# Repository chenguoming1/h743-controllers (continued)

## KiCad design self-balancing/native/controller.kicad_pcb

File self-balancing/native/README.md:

# Current native repair (2026-10-04)

This working native board is the DRC/physical-copper repair of main `491987e`. See [the current repair review](review/usb-routing-491987e/README.md) for exact source hash, checks, measured USB-C orientation skew, and bounded fanout rules.

**Native CAD checks pass, but this is not a regenerated manufacturing release.** Existing P6 Gerbers, supplier reports, manifests and source-hash export guard remain historical and unchanged. Do not fabricate from stale exports or bypass that guard. Component placement, CPL, BOM, schematics and local libraries are preserved.

---

## Historical P6 package description (not qualification of the current native hash)

# R3-S6-P6 controller

**Use this P6 package only. It supersedes all earlier fabrication packages. P5 contained confirmed narrow copper attachments and must not be fabricated.**

This is the final prototype PCB submission package for the 38 × 38 mm, six-layer H743 controller. Its current electrical map, component placement, 67 edge pads, side sockets, corrected supplier CPL and USB pair geometry are retained. Fabricate with the exact settings in `documents/P6-Production-Instructions.txt`; the assembly production approvals listed there must precede assembly.

The whole-board review covers all 85 routed nets and every copper layer. It simplifies coherent paths, removes unnecessary hooks and dead trees, repairs actual copper necks at joins/pads/vias, and retires six redundant signal vias. It retains justified obstacle escapes and the ground returns. The final source has 3,178 track segments and 406 vias, including all 97 ground stitches. It is 61.696 mm shorter than P5. Those counts supplement the actual geometry and visual evidence; they are not the acceptance test by themselves.

## What to use

The paths below are relative to the release ZIP root.

- `native/`: KiCad source, project libraries and the mandatory P6 export guard
- `release/single-board-gerbers/`: the current six-layer Gerbers, plated and nonplated drills, and job file
- `release/assembly/JLC_BOM.csv` and `JLC_CPL.csv`: 35 part groups and 79 placements; the CPL preserves the user's corrections
- `documents/`: schematic, assembly drawing, fabrication review and production instructions
- `native/review/routing-visual-review/index.html`: complete offline net-by-net visual atlas; unzip first, then open this file
- `validation/`: independent native, actual-copper, exported-file and supplier evidence
- `reconstruction/`: reproducible delta and historical input, for audit only; never fabricate that input

The ZIP manifest fixes every included byte. Final source SHA-256: `cf16a6f5ceae65aad217e29eef23a60dbc8f15af743b363df03aa5a42c9c71dc`. The final supplier project is https://jlcdfm.com/viewer?pcbUploadFileId=629361373570224129. Trace width and spacing are green; all three former hole-to-trace advisories cleared. The report gives the evidence-backed dispositions for remaining process/model alerts, including the unchanged 24 red / 6 yellow SMT records. These counts do not constitute assembly production approval.

## Readiness limits

Bare-PCB submission uses a specified supported process. Assembly still requires the supplier's final two-face placement/polarity drawing, a suitable carrier/support arrangement, an approved production stencil, and soldering all four USB shell anchors. The supplier regenerates its stencil, so the real U2/U11 split apertures must be requested explicitly. The package includes the concrete instructions; it does not claim an order or supplier production approval already exists.

First-article inspection and current-limited electrical, thermal, USB/firmware, connector and application tests remain necessary. Compilation and CAD checks do not establish flight readiness or a numerical probability of success.

## Regeneration

Use `native/tools/export_release_p6.py` only with its exact source/evidence guard. It refuses stale source and requires actual join, pad, via, plane and dangling-tree checks. `export_release.py` is the underlying producer, not an alternative release-acceptance path. Preserved older helpers and baselines are historical provenance.

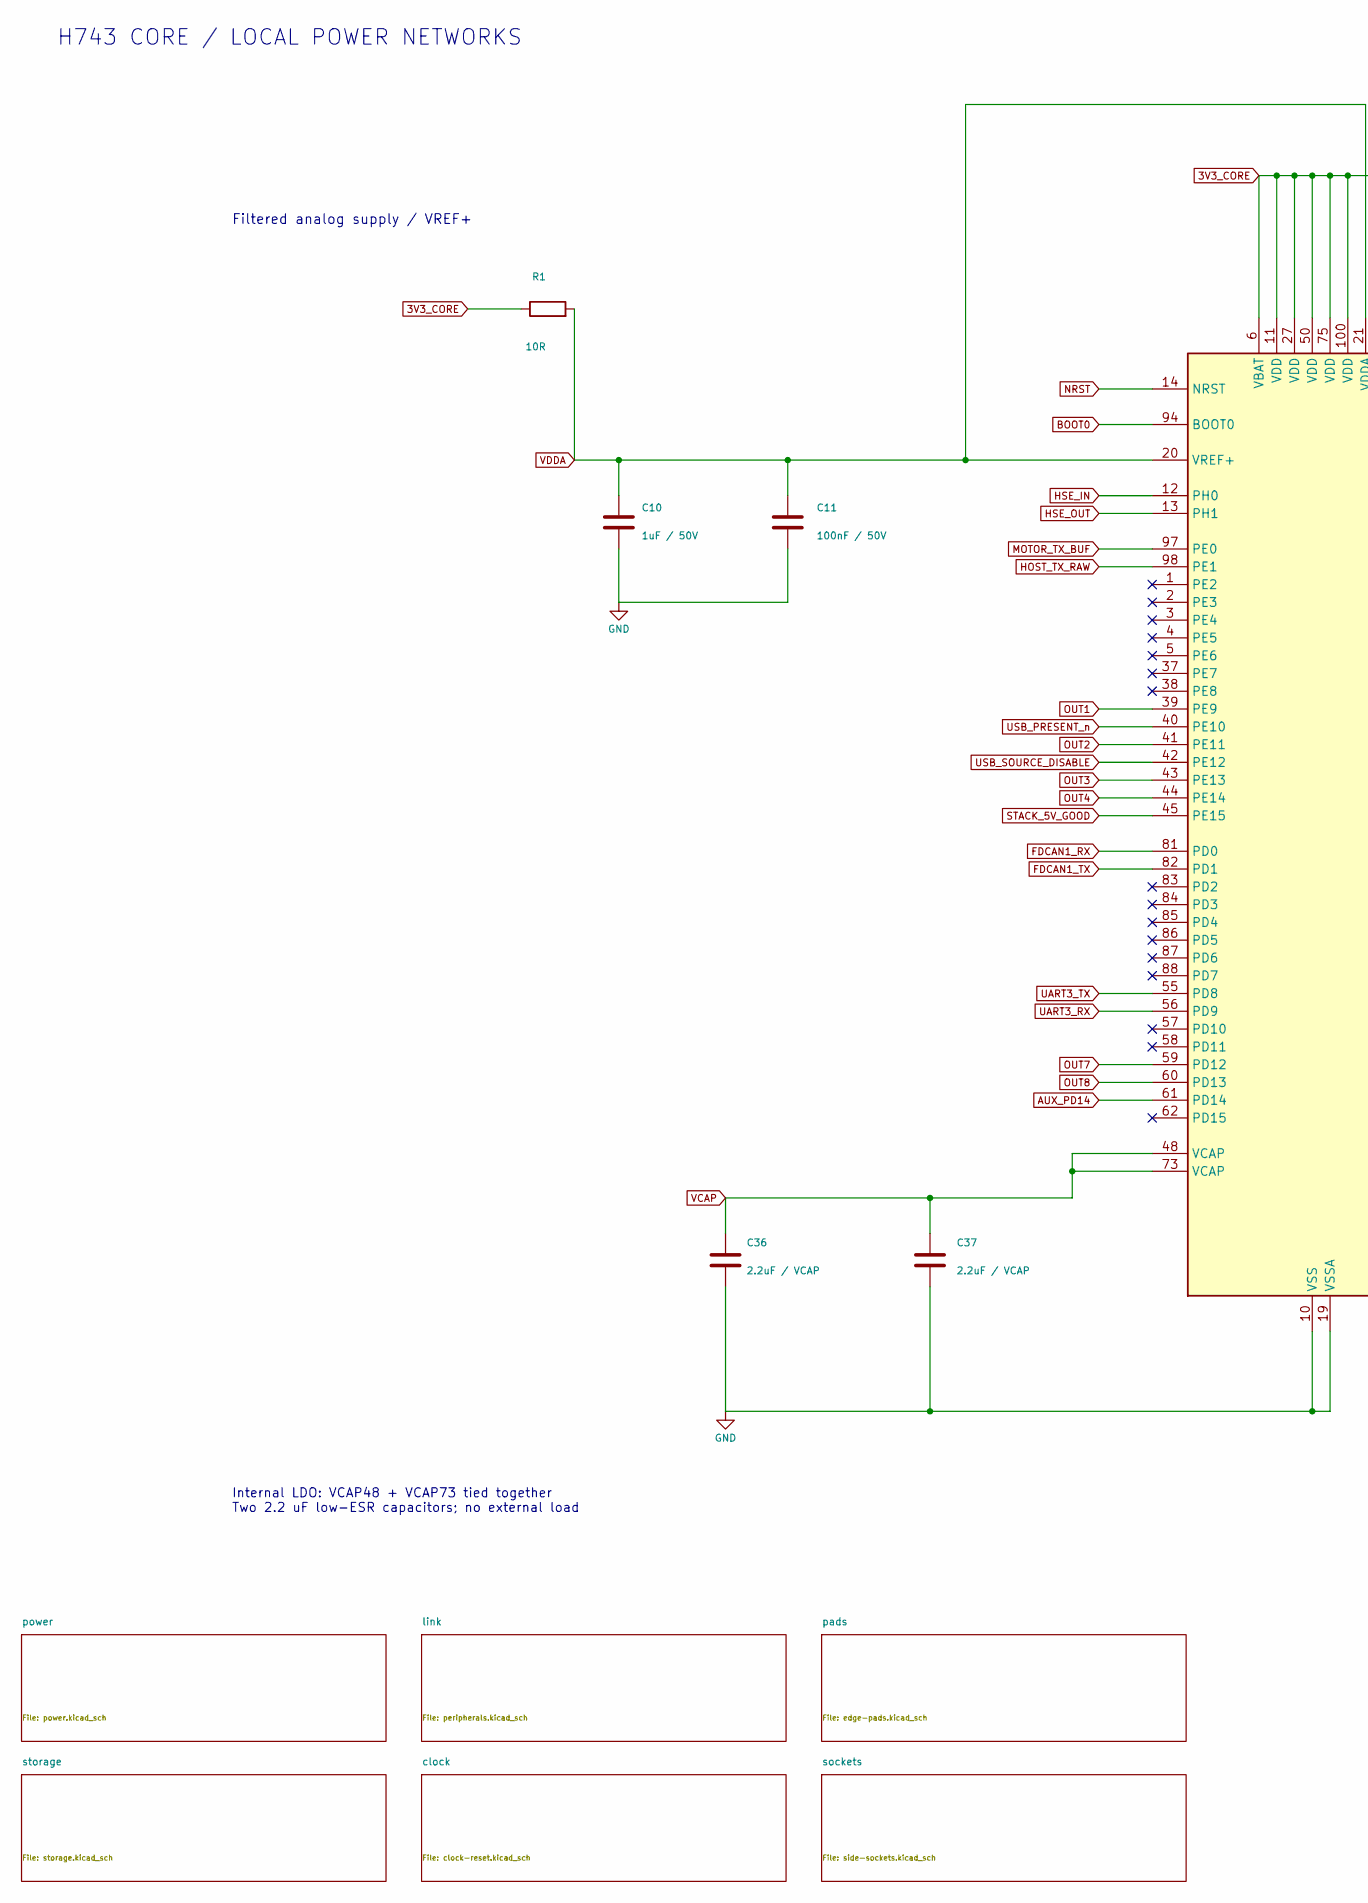
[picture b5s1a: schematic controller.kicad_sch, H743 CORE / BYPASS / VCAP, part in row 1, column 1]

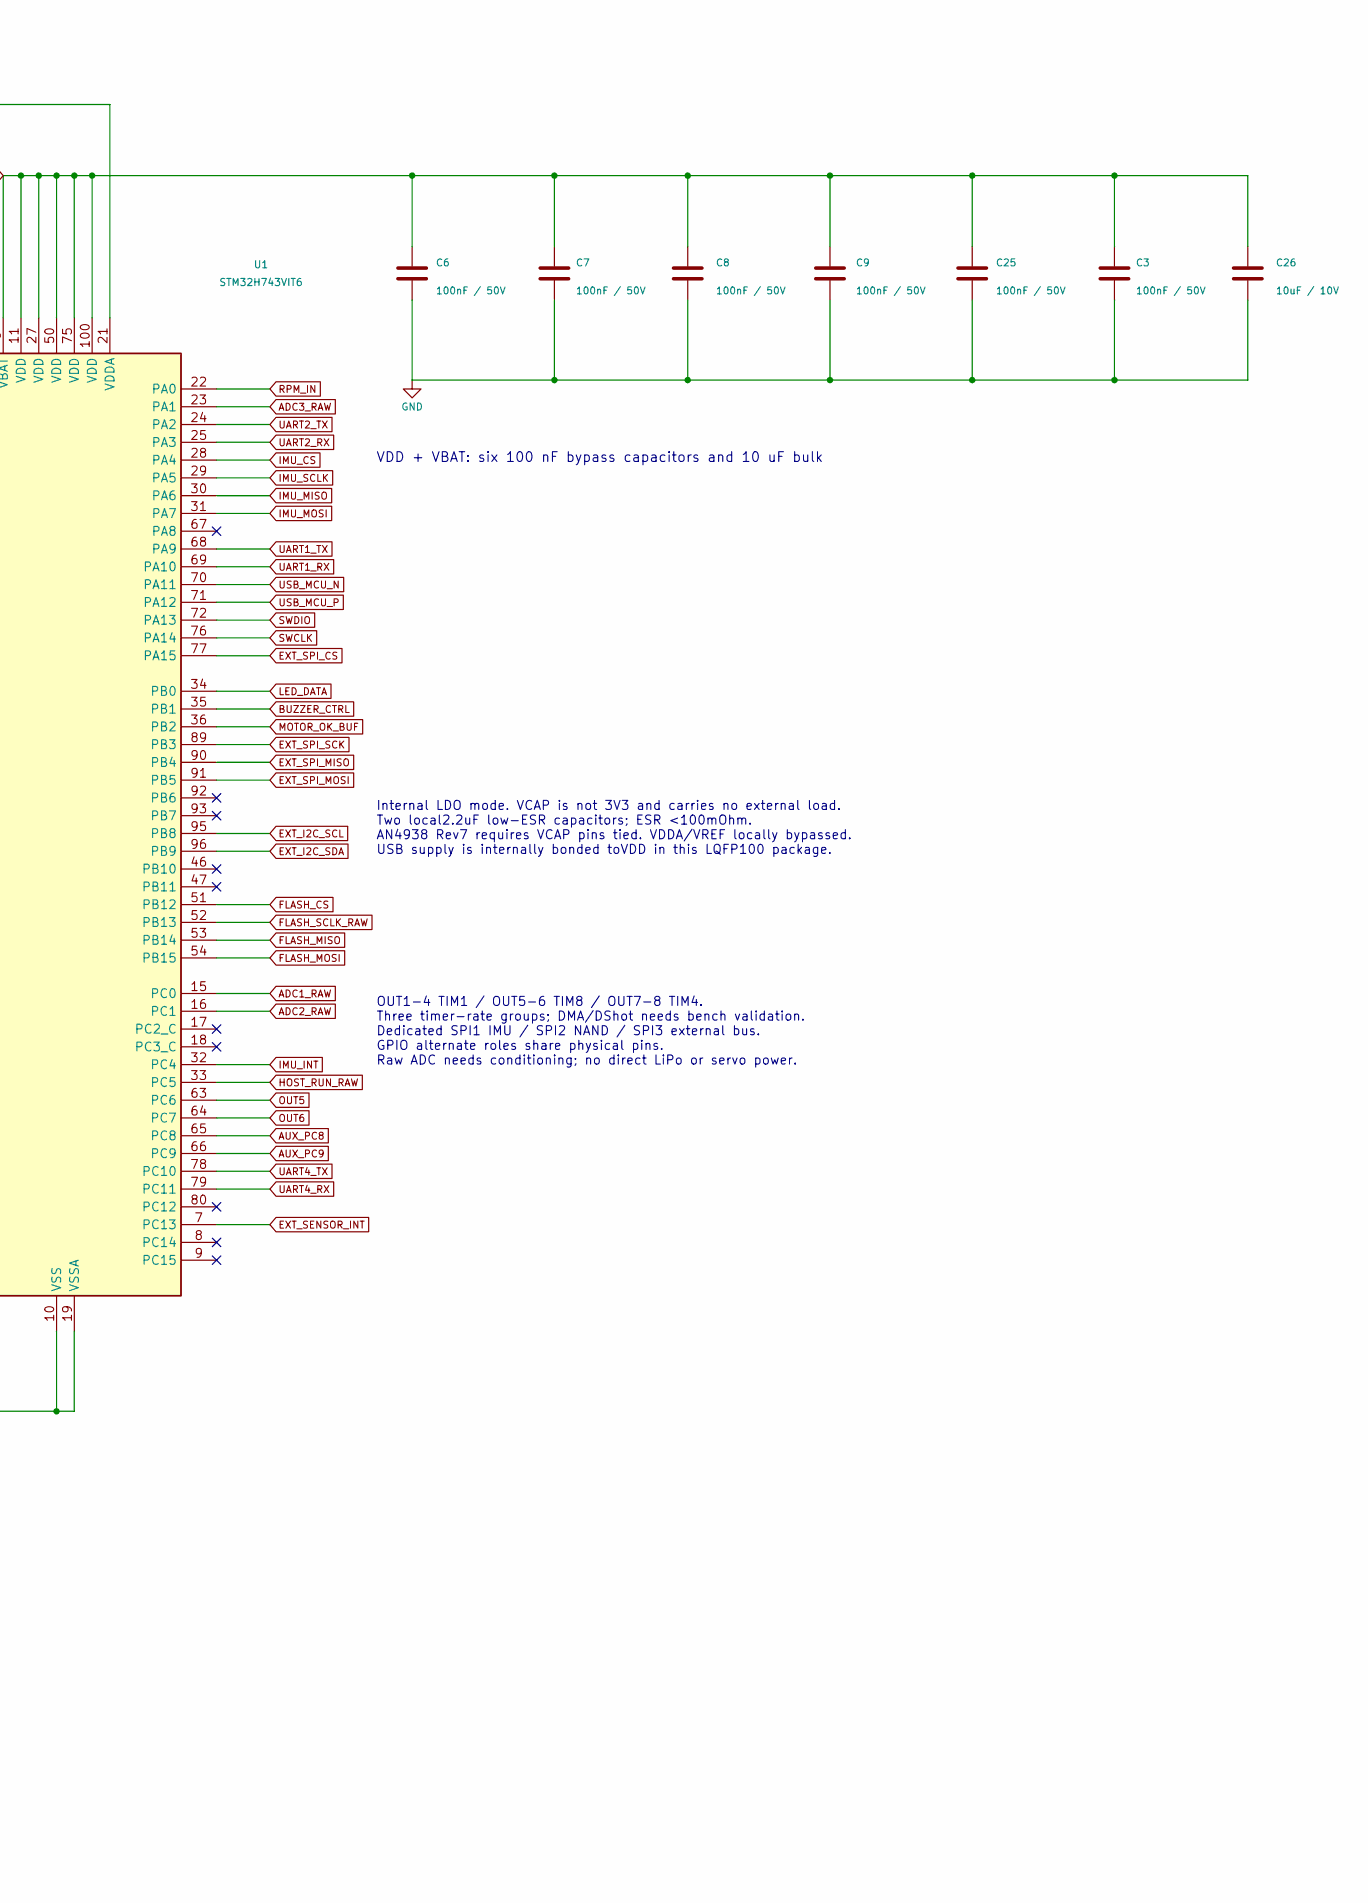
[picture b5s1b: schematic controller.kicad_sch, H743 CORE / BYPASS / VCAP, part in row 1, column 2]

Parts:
C3: 100nF / 50V; C3_C_0603_1608Metric; Manufacturer_Part_Number CC0603KRX7R9BB104; LCSC C14663
C6: 100nF / 50V; C6_C_0603_1608Metric; Manufacturer_Part_Number CC0603KRX7R9BB104; LCSC C14663
C7: 100nF / 50V; C7_C_0603_1608Metric; Manufacturer_Part_Number CC0603KRX7R9BB104; LCSC C14663
C8: 100nF / 50V; C8_C_0603_1608Metric; Manufacturer_Part_Number CC0603KRX7R9BB104; LCSC C14663
C9: 100nF / 50V; C9_C_0603_1608Metric; Manufacturer_Part_Number CC0603KRX7R9BB104; LCSC C14663
C10: 1uF / 50V; C10_C_0603_1608Metric; Manufacturer_Part_Number CL10A105KB8NNNC; LCSC C15849
C11: 100nF / 50V; C11_C_0603_1608Metric; Manufacturer_Part_Number CC0603KRX7R9BB104; LCSC C14663
C25: 100nF / 50V; C25_C_0603_1608Metric; Manufacturer_Part_Number CC0603KRX7R9BB104; LCSC C14663
C26: 10uF / 10V; C26_C_0603_1608Metric; Manufacturer_Part_Number CL10A106KP8NNNC; LCSC C19702
C36: 2.2uF / VCAP; C36_C_0603_1608Metric; Manufacturer_Part_Number CL10A225KO8NNNC; LCSC C23630
C37: 2.2uF / VCAP; C37_C_0603_1608Metric; Manufacturer_Part_Number CL10A225KO8NNNC; LCSC C23630
R1: 10R; R1_R_0603_1608Metric; Manufacturer_Part_Number 0603WAF100JT5E; LCSC C22859
U1: STM32H743VIT6; U1_LQFP-100_14x14mm_P0.5mm; Manufacturer_Part_Number STM32H743VIT6; LCSC C114409

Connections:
ADC1_RAW: U1.15 (PC0); also elsewhere on the board
ADC2_RAW: U1.16 (PC1); also elsewhere on the board
ADC3_RAW: U1.23 (PA1); also elsewhere on the board
AUX_PC8: U1.65 (PC8); also elsewhere on the board
AUX_PC9: U1.66 (PC9); also elsewhere on the board
AUX_PD14: U1.61 (PD14); also elsewhere on the board
BOOT0: U1.94 (BOOT0); also elsewhere on the board
BUZZER_CTRL: U1.35 (PB1); also elsewhere on the board
EXT_I2C_SCL: U1.95 (PB8); also elsewhere on the board
EXT_I2C_SDA: U1.96 (PB9); also elsewhere on the board
EXT_SENSOR_INT: U1.7 (PC13); also elsewhere on the board
EXT_SPI_CS: U1.77 (PA15); also elsewhere on the board
EXT_SPI_MISO: U1.90 (PB4); also elsewhere on the board
EXT_SPI_MOSI: U1.91 (PB5); also elsewhere on the board
EXT_SPI_SCK: U1.89 (PB3); also elsewhere on the board
FDCAN1_RX: U1.81 (PD0); also elsewhere on the board
FDCAN1_TX: U1.82 (PD1); also elsewhere on the board
FLASH_MISO: U1.53 (PB14); also elsewhere on the board
FLASH_MOSI: U1.54 (PB15); also elsewhere on the board
FLASH_SCLK_RAW: U1.52 (PB13); also elsewhere on the board
GND: C3.2, C6.2, C7.2, C8.2, C9.2, C10.2, C11.2, C25.2, C26.2, C36.2, C37.2, U1.10 (VSS), U1.19 (VSSA), U1.26 (VSS), U1.49 (VSS), U1.74 (VSS), U1.99 (VSS); also elsewhere on the board
HOST_RUN_RAW: U1.33 (PC5); also elsewhere on the board
HOST_TX_RAW: U1.98 (PE1); also elsewhere on the board
HSE_IN: U1.12 (PH0); also elsewhere on the board
HSE_OUT: U1.13 (PH1); also elsewhere on the board
IMU_CS: U1.28 (PA4); also elsewhere on the board
IMU_INT: U1.32 (PC4); also elsewhere on the board
IMU_MISO: U1.30 (PA6); also elsewhere on the board
IMU_MOSI: U1.31 (PA7); also elsewhere on the board
IMU_SCLK: U1.29 (PA5); also elsewhere on the board
LED_DATA: U1.34 (PB0); also elsewhere on the board
MOTOR_OK_BUF: U1.36 (PB2); also elsewhere on the board
MOTOR_TX_BUF: U1.97 (PE0); also elsewhere on the board
NRST: U1.14 (NRST); also elsewhere on the board
OUT1: U1.39 (PE9); also elsewhere on the board
OUT2: U1.41 (PE11); also elsewhere on the board
OUT3: U1.43 (PE13); also elsewhere on the board
OUT4: U1.44 (PE14); also elsewhere on the board
OUT5: U1.63 (PC6); also elsewhere on the board
OUT6: U1.64 (PC7); also elsewhere on the board
OUT7: U1.59 (PD12); also elsewhere on the board
OUT8: U1.60 (PD13); also elsewhere on the board
RPM_IN: U1.22 (PA0); also elsewhere on the board
STACK_5V_GOOD: U1.45 (PE15); also elsewhere on the board
SWCLK: U1.76 (PA14); also elsewhere on the board
SWDIO: U1.72 (PA13); also elsewhere on the board
UART1_RX: U1.69 (PA10); also elsewhere on the board
UART1_TX: U1.68 (PA9); also elsewhere on the board
UART2_RX: U1.25 (PA3); also elsewhere on the board
UART2_TX: U1.24 (PA2); also elsewhere on the board
UART3_RX: U1.56 (PD9); also elsewhere on the board
UART3_TX: U1.55 (PD8); also elsewhere on the board
UART4_RX: U1.79 (PC11); also elsewhere on the board
UART4_TX: U1.78 (PC10); also elsewhere on the board
USB_MCU_N: U1.70 (PA11); also elsewhere on the board
USB_MCU_P: U1.71 (PA12); also elsewhere on the board
USB_PRESENT_n: U1.40 (PE10); also elsewhere on the board
USB_SOURCE_DISABLE: U1.42 (PE12); also elsewhere on the board
VCAP: C36.1, C37.1, U1.48 (VCAP), U1.73 (VCAP)
VDDA: C10.1, C11.1, R1.2, U1.20 (VREF+), U1.21 (VDDA)

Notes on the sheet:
H743 CORE / LOCAL POWER NETWORKS
VDD + VBAT: six 100 nF bypass capacitors and 10 uF bulk
Filtered analog supply / VREF+
Internal LDO: VCAP48 + VCAP73 tied together Two 2.2 uF low-ESR capacitors; no external load
Internal LDO mode. VCAP is not 3V3 and carries no external load. Two local2.2uF low-ESR capacitors; ESR <100mOhm. AN4938 Rev7 requires VCAP pins tied. VDDA/VREF locally bypassed. USB supply is internally bonded toVDD in this LQFP100 package.
OUT1-4 TIM1 / OUT5-6 TIM8 / OUT7-8 TIM4. Three timer-rate groups; DMA/DShot needs bench validation. Dedicated SPI1 IMU / SPI2 NAND / SPI3 external bus. GPIO alternate roles share physical pins. Raw ADC needs conditioning; no direct LiPo or servo power.

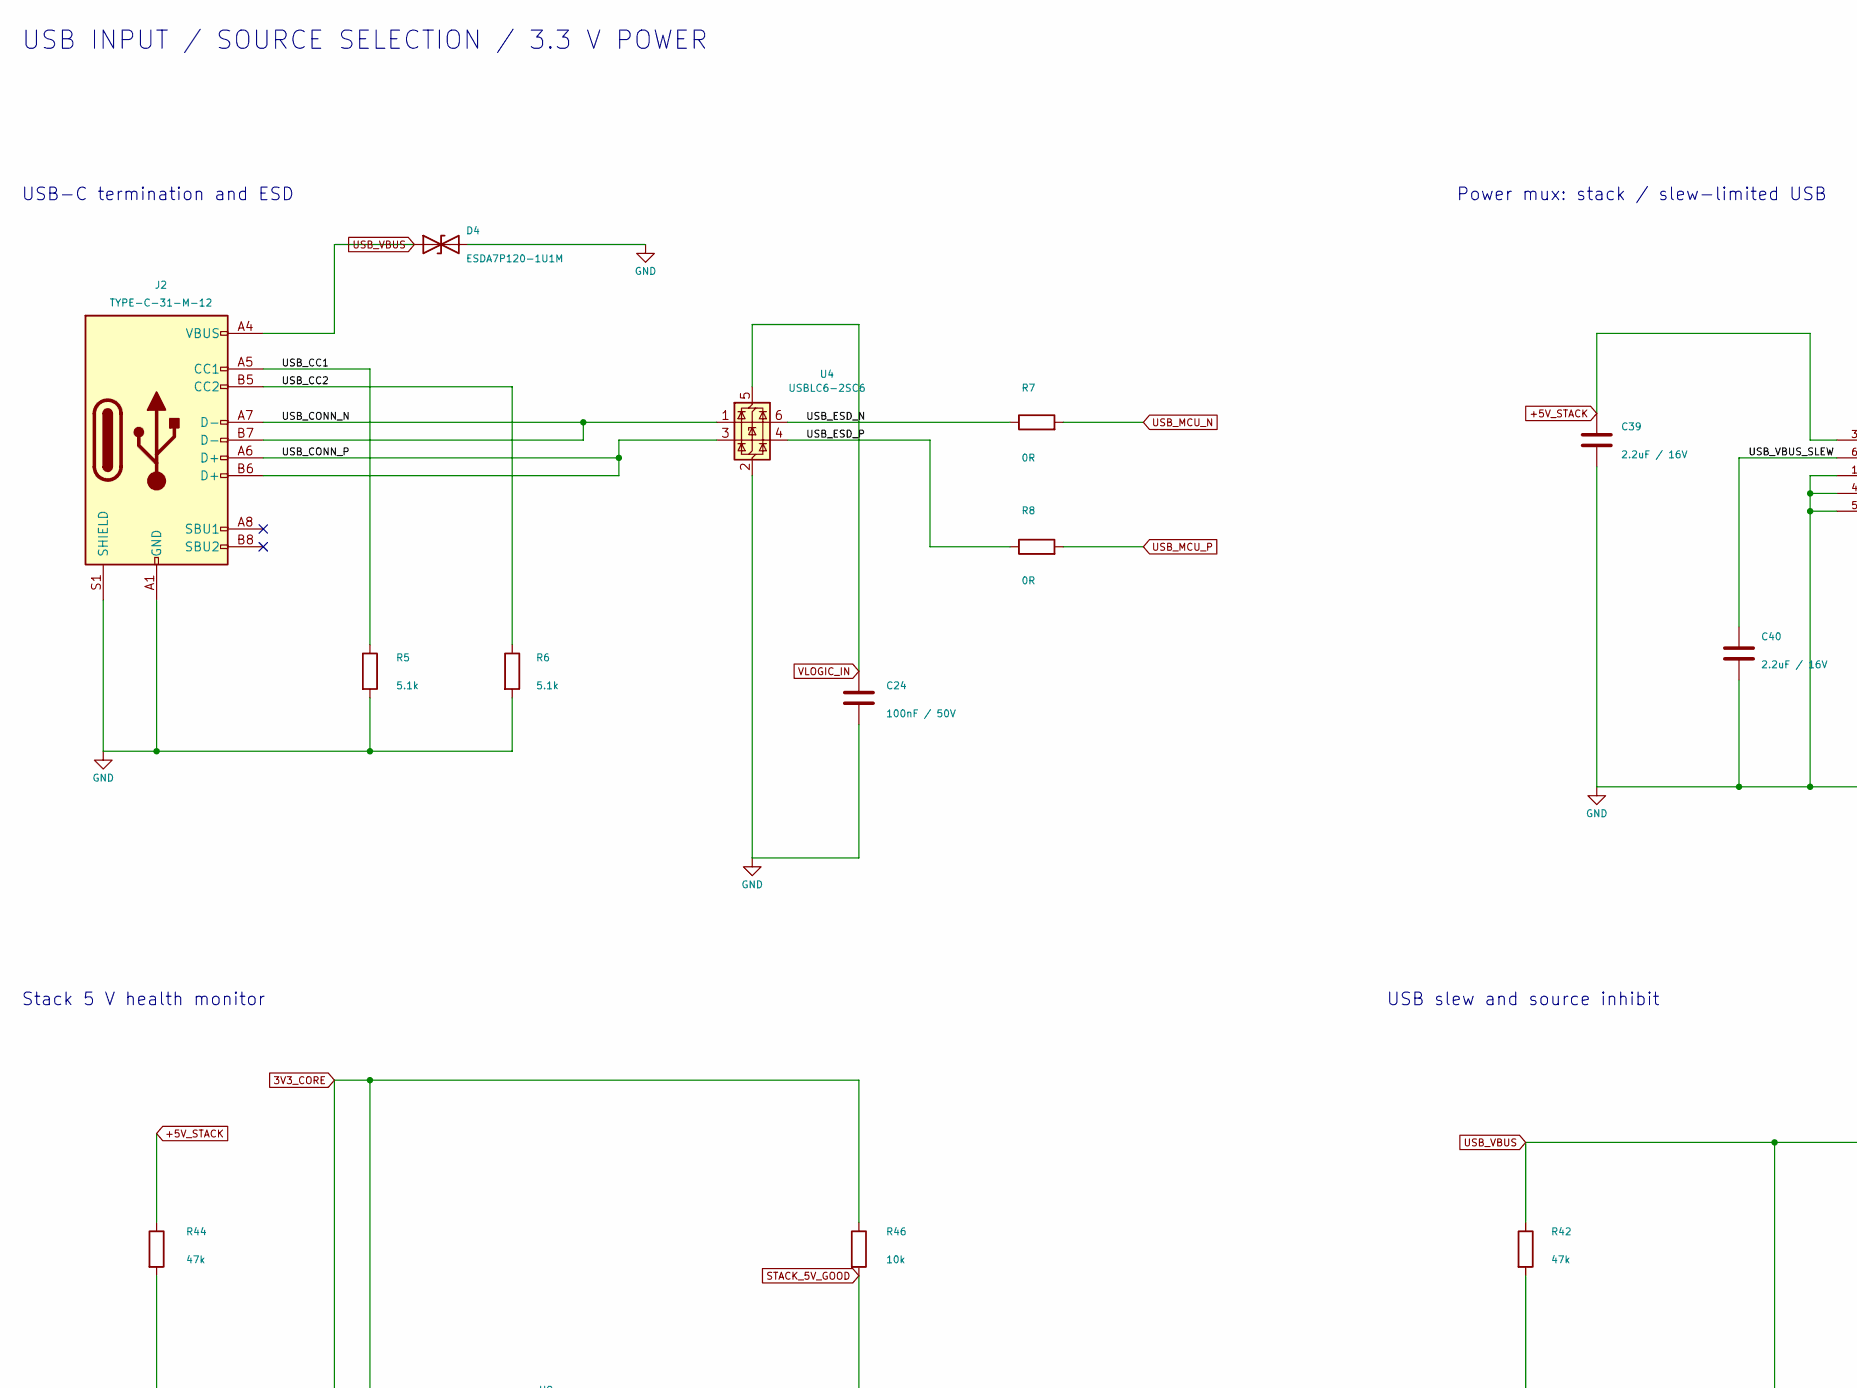
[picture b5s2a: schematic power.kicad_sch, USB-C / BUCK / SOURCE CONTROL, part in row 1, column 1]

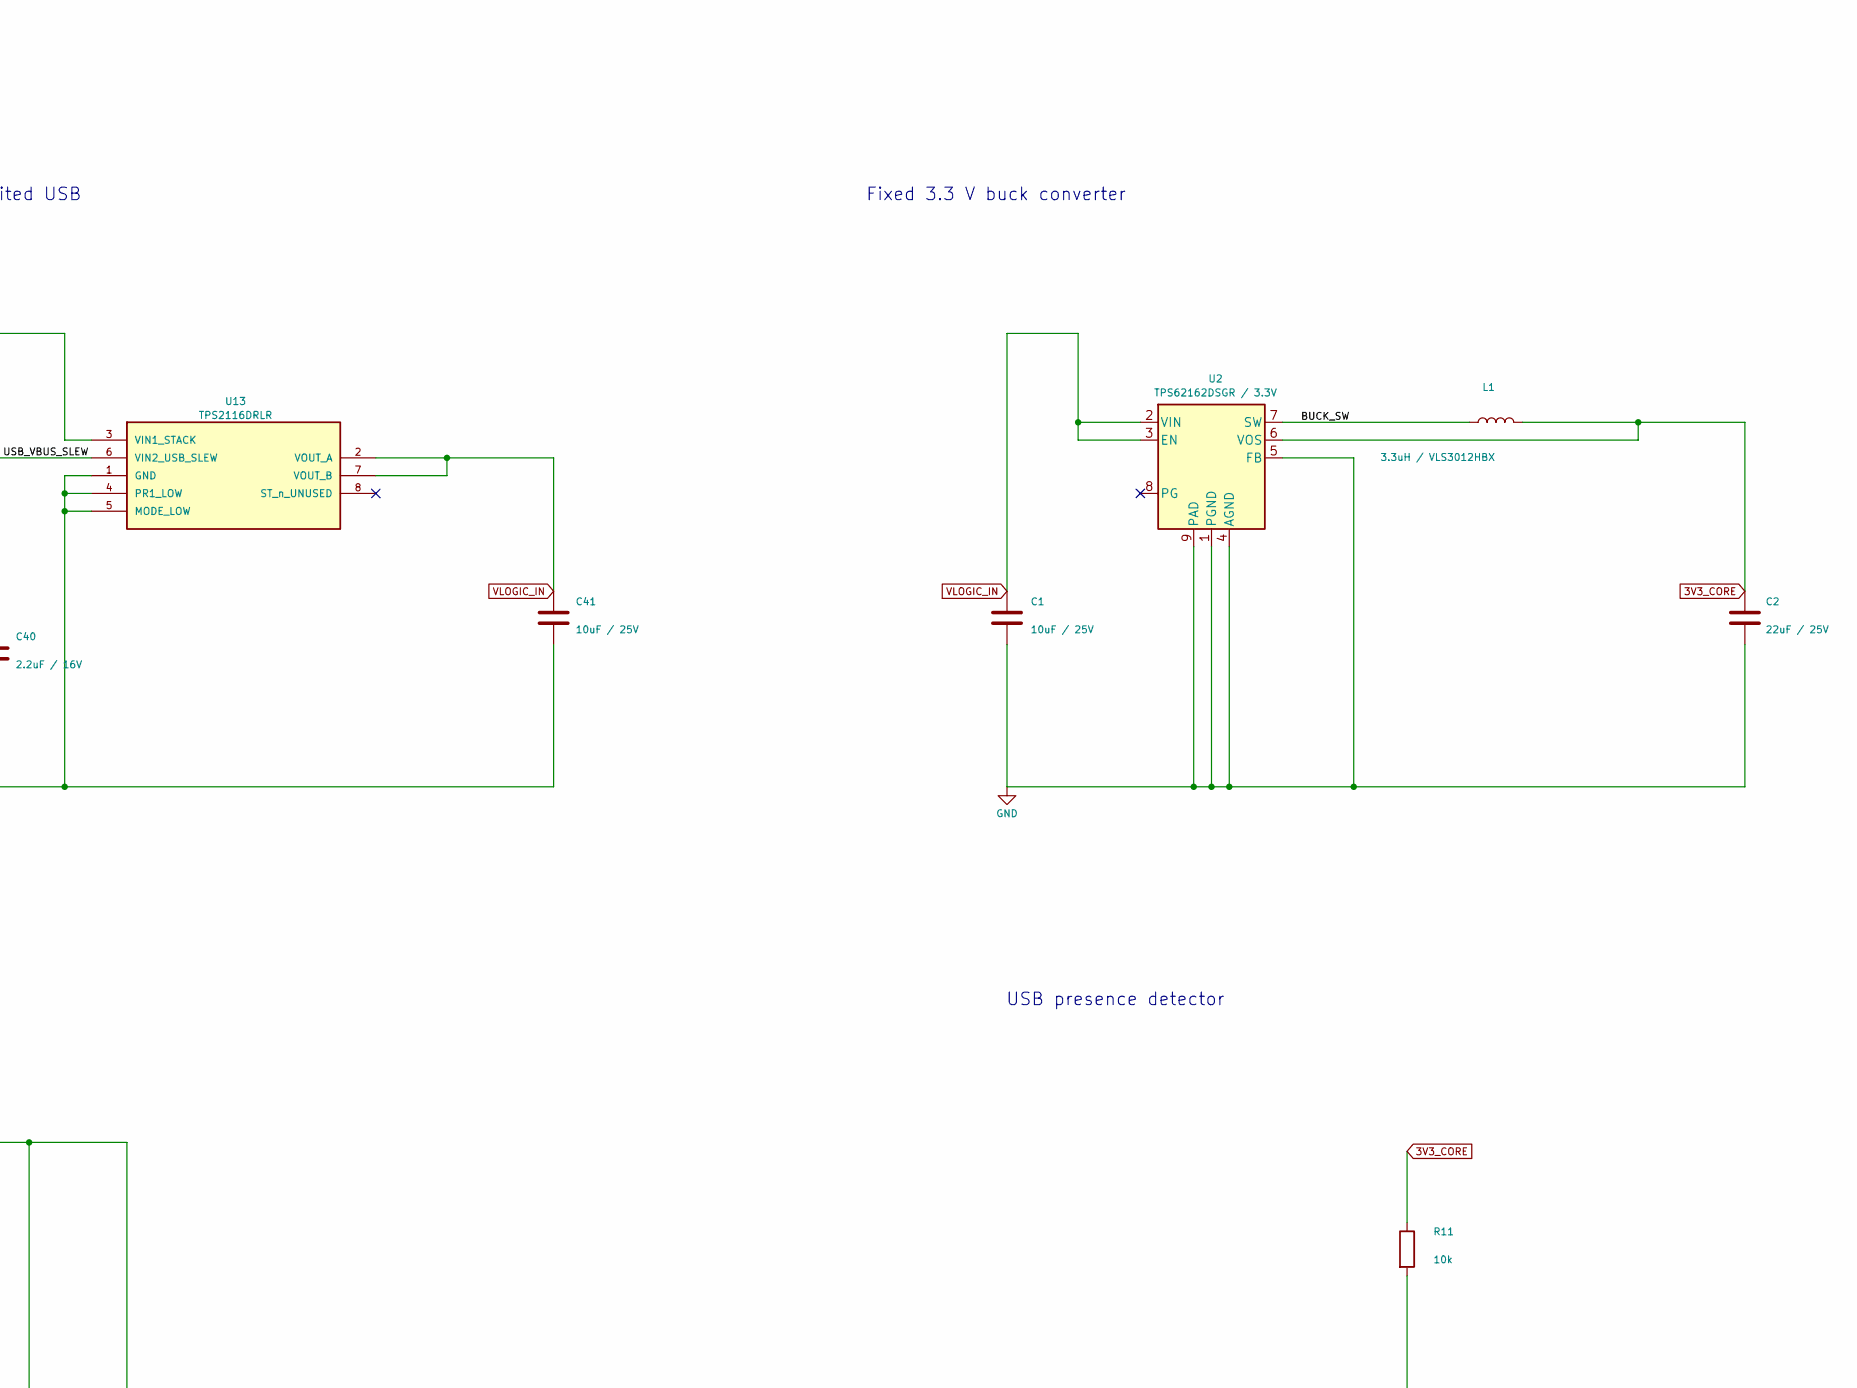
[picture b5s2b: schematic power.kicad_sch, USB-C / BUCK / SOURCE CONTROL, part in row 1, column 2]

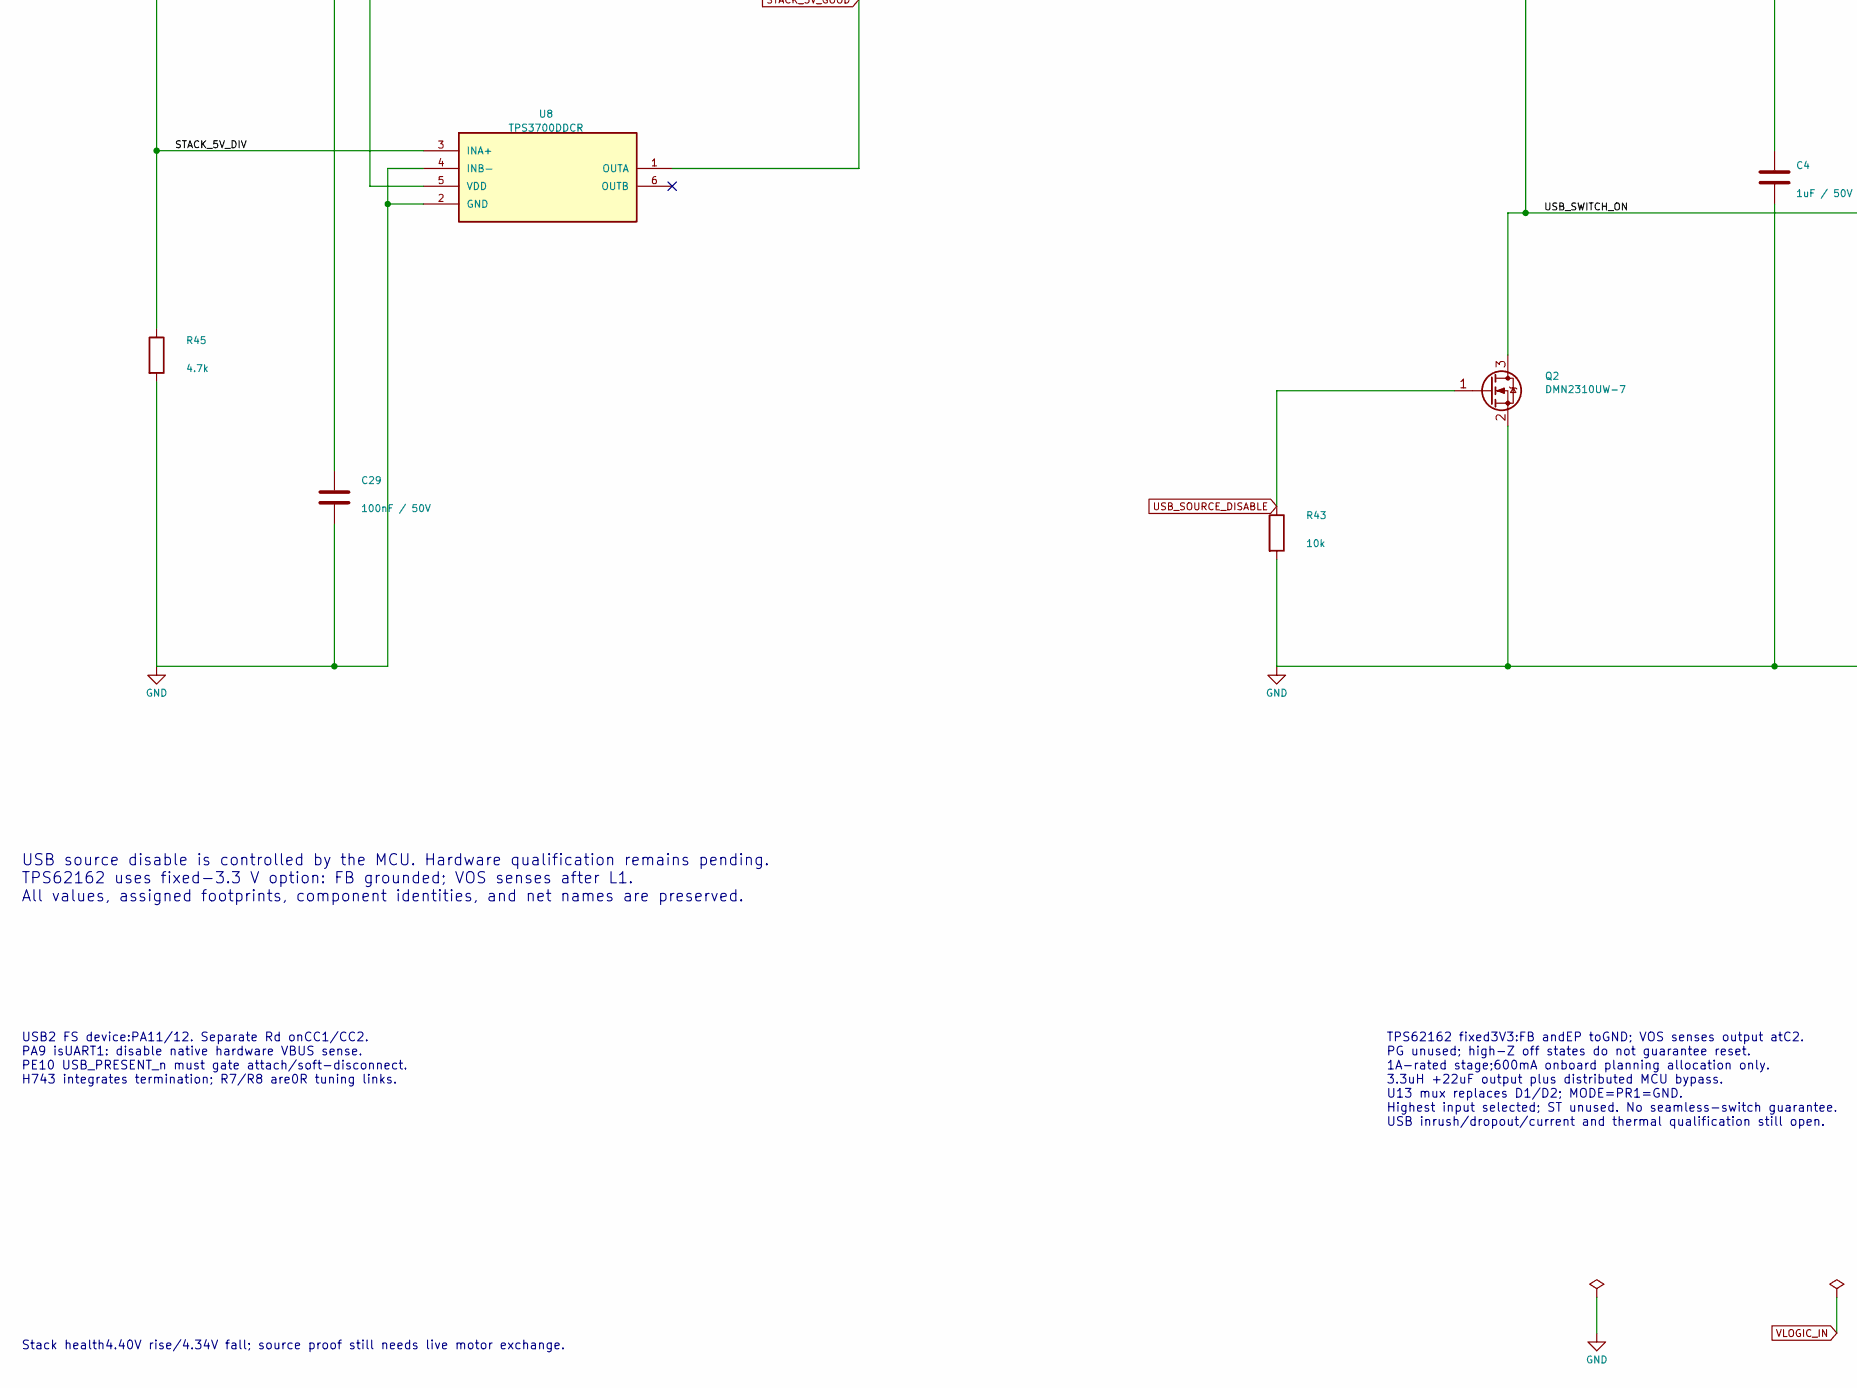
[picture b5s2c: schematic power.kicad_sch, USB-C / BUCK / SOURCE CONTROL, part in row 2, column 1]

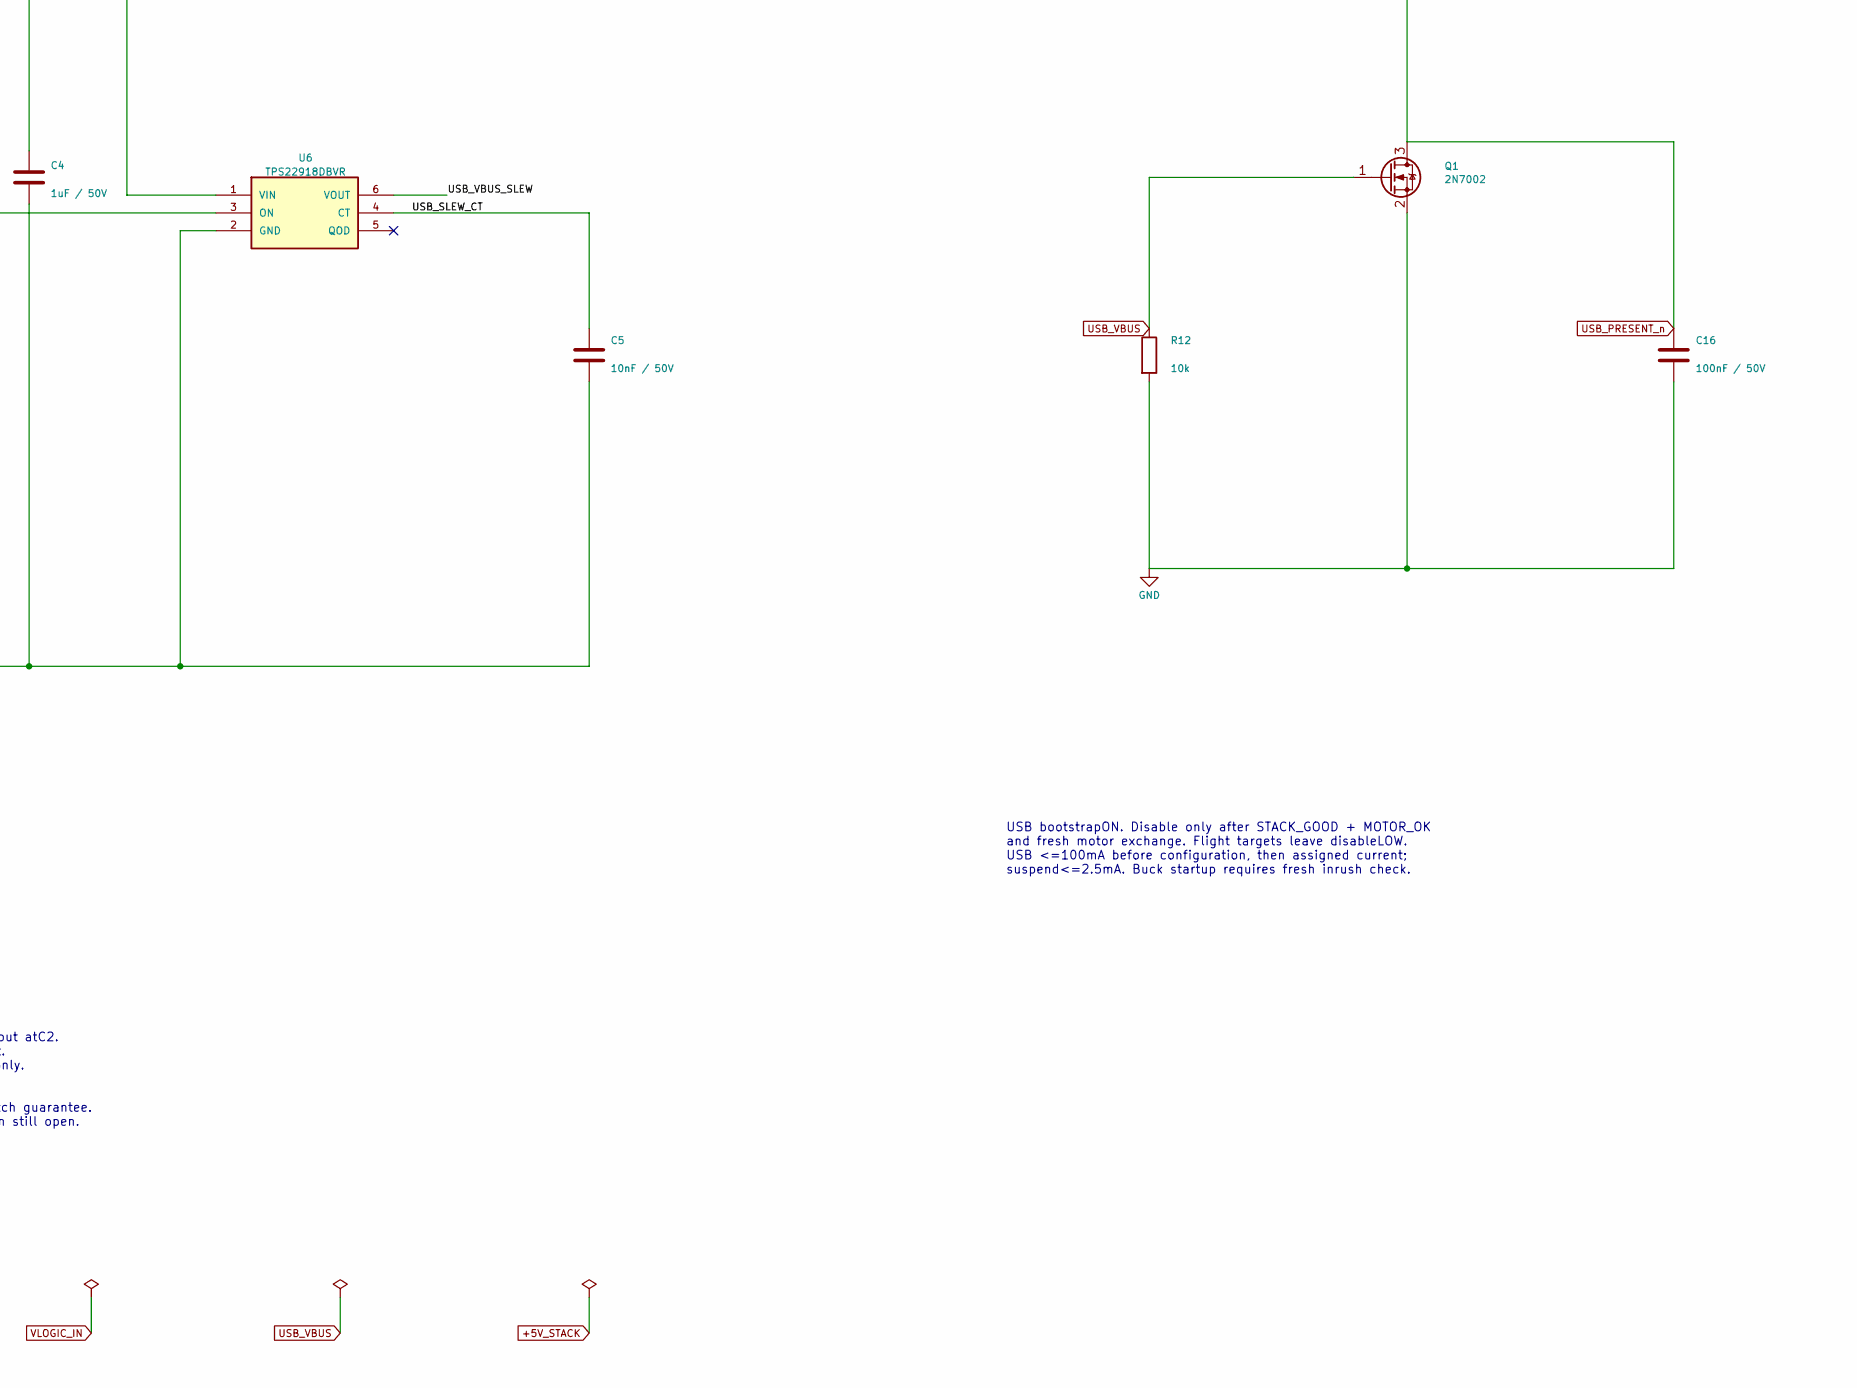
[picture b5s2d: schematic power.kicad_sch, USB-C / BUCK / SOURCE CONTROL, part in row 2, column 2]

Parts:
C1: 10uF / 25V; C1_C_0805_2012Metric; Manufacturer_Part_Number CL21A106KAYNNNE; LCSC C15850
C2: 22uF / 25V; C2_C_1206_3216Metric; Manufacturer_Part_Number CL31A226KAHNNNE; LCSC C12891
C4: 1uF / 50V; C4_C_0603_1608Metric; Manufacturer_Part_Number CL10A105KB8NNNC; LCSC C15849
C5: 10nF / 50V; C5_C_0603_1608Metric; Manufacturer_Part_Number 0603B103K500NT; LCSC C57112
C16: 100nF / 50V; C16_C_0603_1608Metric; Manufacturer_Part_Number CC0603KRX7R9BB104; LCSC C14663
C24: 100nF / 50V; C24_C_0603_1608Metric; Manufacturer_Part_Number CC0603KRX7R9BB104; LCSC C14663
C29: 100nF / 50V; C29_C_0603_1608Metric; Manufacturer_Part_Number CC0603KRX7R9BB104; LCSC C14663
C39: 2.2uF / 16V; C39_C_0603_1608Metric; Manufacturer_Part_Number CL10A225KO8NNNC; LCSC C23630
C40: 2.2uF / 16V; C40_C_0603_1608Metric; Manufacturer_Part_Number CL10A225KO8NNNC; LCSC C23630
C41: 10uF / 25V; C41_C_0805_2012Metric; Manufacturer_Part_Number CL21A106KAYNNNE; LCSC C15850
D4: ESDA7P120-1U1M; ST_QFN-2L_1.6x1.0mm_DS14419; Manufacturer_Part_Number ESDA7P120-1U1M; LCSC C2969802
J2: TYPE-C-31-M-12; USB_C_HRO_TYPE-C-31-M-12_EdgeSilk; Manufacturer_Part_Number TYPE-C-31-M-12; LCSC C165948
L1: 3.3uH / VLS3012HBX; TDK_VLS3012HBX; Manufacturer_Part_Number VLS3012HBX-3R3M; LCSC C404495
Q1: 2N7002; Q1_SOT-23; Manufacturer_Part_Number 2N7002; LCSC C8545
Q2: DMN2310UW-7; DMN2310UW_SOT323; Manufacturer_Part_Number DMN2310UW-7; LCSC C7264627
R5: 5.1k; R5_R_0603_1608Metric; Manufacturer_Part_Number 0603WAF5101T5E; LCSC C23186
R6: 5.1k; R6_R_0603_1608Metric; Manufacturer_Part_Number 0603WAF5101T5E; LCSC C23186
R7, R8: 0R; R_0402_1005Metric_R3S_NoSilk; Manufacturer_Part_Number 0402WGF0000TCE; LCSC C17168
R11: 10k; R11_R_0603_1608Metric; Manufacturer_Part_Number 0603WAF1002T5E; LCSC C25804
R12: 10k; R12_R_0603_1608Metric; Manufacturer_Part_Number 0603WAF1002T5E; LCSC C25804
R42: 47k; R42_R_0603_1608Metric; Manufacturer_Part_Number 0603WAF4702T5E; LCSC C25819
R43: 10k; R43_R_0603_1608Metric; Manufacturer_Part_Number 0603WAF1002T5E; LCSC C25804
R44: 47k; R44_R_0603_1608Metric; Manufacturer_Part_Number 0603WAF4702T5E; LCSC C25819
R45: 4.7k; R45_R_0603_1608Metric; Manufacturer_Part_Number 0603WAF4701T5E; LCSC C23162
R46: 10k; R46_R_0603_1608Metric; Manufacturer_Part_Number 0603WAF1002T5E; LCSC C25804
U2: TPS62162DSGR / 3.3V; TPS62162_DSG_R3S; Manufacturer_Part_Number TPS62162DSGR; LCSC C40256
U4: USBLC6-2SC6; U4_SOT-23-6; Manufacturer_Part_Number USBLC6-2SC6; LCSC C7519
U6: TPS22918DBVR; U6_SOT-23-6; Manufacturer_Part_Number TPS22918DBVR; LCSC C131941
U8: TPS3700DDCR; TSOT-23-6_R3S_ClearLabels; Manufacturer_Part_Number TPS3700DDCR; LCSC C33002
U13: TPS2116DRLR; U13_SOT-583-8; Manufacturer_Part_Number TPS2116DRLR; LCSC C3235557

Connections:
+5V_STACK: C39.1, R44.1, U13.3 (VIN1_STACK); also elsewhere on the board
/power/BUCK_SW: L1.1, U2.7 (SW)
/power/STACK_5V_DIV: R44.2, R45.1, U8.3 (INA+)
/power/USB_CC1: J2.A5 (CC1), R5.1
/power/USB_CC2: J2.B5 (CC2), R6.1
/power/USB_CONN_N: J2.A7 (D-), J2.B7 (D-), U4.1 (I/O1)
/power/USB_CONN_P: J2.A6 (D+), J2.B6 (D+), U4.3 (I/O2)
/power/USB_ESD_N: R7.1, U4.6 (I/O1)
/power/USB_ESD_P: R8.1, U4.4 (I/O2)
/power/USB_SLEW_CT: C5.1, U6.4 (CT)
/power/USB_SWITCH_ON: Q2.3 (D), R42.2, U6.3 (ON)
/power/USB_VBUS_SLEW: C40.1, U6.6 (VOUT), U13.6 (VIN2_USB_SLEW)
GND: C1.2, C2.2, C4.2, C5.2, C16.2, C24.2, C29.2, C39.2, C40.2, C41.2, D4.2 (A2), J2.A1 (GND), J2.A12 (GND), J2.B1 (GND), J2.B12 (GND), J2.S1 (SHIELD), Q1.2 (S), Q2.2 (S), R5.2, R6.2, R12.2, R43.2, R45.2, U2.1 (PGND), U2.4 (AGND), U2.5 (FB), U2.9 (PAD), U4.2 (GND), U6.2 (GND), U8.2 (GND), U8.4 (INB-), U13.1 (GND), U13.4 (PR1_LOW), U13.5 (MODE_LOW); also elsewhere on the board
STACK_5V_GOOD: R46.2, U8.1 (OUTA); also elsewhere on the board
USB_MCU_N: R7.2; also elsewhere on the board
USB_MCU_P: R8.2; also elsewhere on the board
USB_PRESENT_n: C16.1, Q1.3 (D), R11.2; also elsewhere on the board
USB_SOURCE_DISABLE: Q2.1 (G), R43.1; also elsewhere on the board
USB_VBUS: C4.1, D4.1 (A1), J2.A4 (VBUS), J2.A9 (VBUS), J2.B4 (VBUS), J2.B9 (VBUS), Q1.1 (G), R12.1, R42.1, U6.1 (VIN)
VLOGIC_IN: C1.1, C24.1, C41.1, U2.2 (VIN), U2.3 (EN), U4.5 (VBUS), U13.2 (VOUT_A), U13.7 (VOUT_B)

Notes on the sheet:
USB INPUT / SOURCE SELECTION / 3.3 V POWER
USB-C termination and ESD
Power mux: stack / slew-limited USB
Fixed 3.3 V buck converter
Stack 5 V health monitor
USB slew and source inhibit
USB presence detector
USB source disable is controlled by the MCU. Hardware qualification remains pending. TPS62162 uses fixed-3.3 V option: FB grounded; VOS senses after L1. All values, assigned footprints, component identities, and net names are preserved.
USB2 FS device:PA11/12. Separate Rd onCC1/CC2. PA9 isUART1: disable native hardware VBUS sense. PE10 USB_PRESENT_n must gate attach/soft-disconnect. H743 integrates termination; R7/R8 are0R tuning links.
TPS62162 fixed3V3:FB andEP toGND; VOS senses output atC2. PG unused; high-Z off states do not guarantee reset. 1A-rated stage;600mA onboard planning allocation only. 3.3uH +22uF output plus distributed MCU bypass. U13 mux replaces D1/D2; MODE=PR1=GND. Highest input selected; ST unused. No seamless-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
USB bootstrapON. Disable only after STACK_GOOD + MOTOR_OK and fresh motor exchange. Flight targets leave disableLOW. USB <=100mA before configuration, then assigned current; suspend<=2.5mA. Buck startup requires fresh inrush check.
Stack health4.40V rise/4.34V fall; source proof still needs live motor exchange.
